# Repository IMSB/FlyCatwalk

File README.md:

FlyCatwalk
==========
This repository contains basic documentation, drawings and code for the **FlyCatwalk**, which was originally developed as a collaboration between the [Institute of Molecular Systems Biology](http://www.imsb.ethz.ch/) at [ETH Zürich](http://www.ethz.ch) and [Scitracks GmbH](http://www.scitracks.com/) 

### License
The **FlyCatwalk** package is licensed by [ETH Zürich](http://www.ethz.ch) under [GPLv3 license](http://www.gnu.org/copyleft/gpl.html)

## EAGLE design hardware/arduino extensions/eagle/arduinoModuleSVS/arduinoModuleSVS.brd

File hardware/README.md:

Hardware
==========
Contains the cad files and the schematics of the arduino extensions required to build the flycatwalk.
The cutting work was done with a laser cutter.

### License
The **FlyCatwalk** package is licensed by [ETH Zürich](http://www.ethz.ch) under [GPLv3 license](http://www.gnu.org/copyleft/gpl.html)

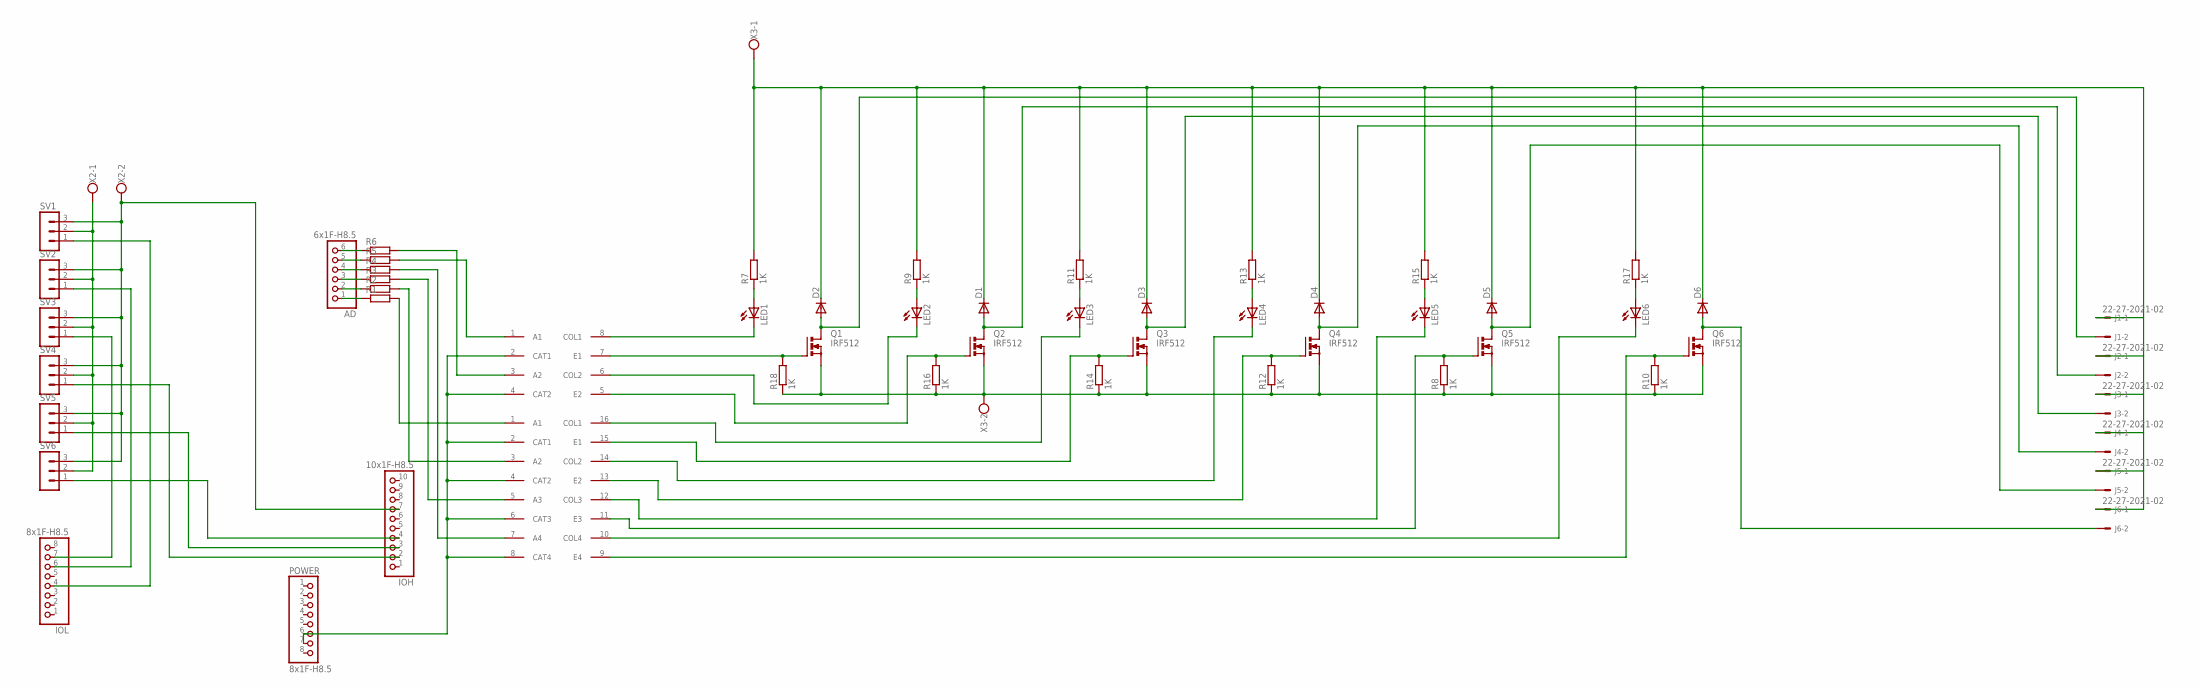
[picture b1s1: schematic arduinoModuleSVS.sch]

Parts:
AD: 6x1F-H8.5; SMARTPRJ_1X06
D1, D2, D3, D4, D5, D6: DIODE-SOD123; SOD123
IOH: 10x1F-H8.5; SMARTPRJ_1X10
IOL: 8x1F-H8.5; SMARTPRJ_1X08
J1, J2, J3, J4, J5, J6: 22-27-2021-02; 6410-02
LED1, LED2, LED3, LED4, LED5, LED6: LED3MM
POWER: 8x1F-H8.5; SMARTPRJ_1X08
Q1, Q2, Q3, Q4, Q5, Q6: IRF512; TO220BV
R1, R2, R3, R4, R5, R6: R-EU_R0805; R0805
R7, R8, R9, R10, R11, R12, R13, R14, R15, R16, R17, R18: 1K; R0805
SV1, SV2, SV3, SV4, SV5, SV6: MA03-1
U$1: ACPL-847-W00E; DIL16
U$2: ACPL-827-00CE; DIL08
X2, X3: W237-102

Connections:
GND: POWER.6, POWER.7, U$1.2 (CAT1), U$1.4 (CAT2), U$1.6 (CAT3), U$1.8 (CAT4), U$2.2 (CAT1), U$2.4 (CAT2)
GND24V: Q1.S, Q2.S, Q3.S, Q4.S, Q5.S, Q6.S, R8.1, R10.1, R12.1, R14.1, R16.1, R18.1, X3.2
GNDARDUINO: IOH.7, SV1.3, SV2.3, SV3.3, SV4.3, SV5.3, SV6.3, X2.2
unnamed: IOL.4, SV1.1
unnamed: IOL.6, SV2.1
unnamed: IOL.7, SV3.1
unnamed: IOH.2, SV4.1
unnamed: IOH.3, SV5.1
unnamed: IOH.4, SV6.1
unnamed: R1.2, U$1.1 (A1)
unnamed: R2.2, U$1.3 (A2)
unnamed: R3.2, U$1.5 (A3)
unnamed: AD.1, R1.1
unnamed: R4.2, U$1.7 (A4)
unnamed: AD.2, R2.1
unnamed: AD.3, R3.1
unnamed: AD.4, R4.1
unnamed: R6.2, U$2.3 (A2)
unnamed: R5.2, U$2.1 (A1)
unnamed: AD.6, R6.1
unnamed: AD.5, R5.1
unnamed: Q1.G, R18.2, U$2.7 (E1)
unnamed: D2.A, J1.2, Q1.D
unnamed: LED2.K (C), U$2.6 (COL2)
unnamed: LED2.A, R9.1
unnamed: Q2.G, R16.2, U$2.5 (E2)
unnamed: LED1.K (C), U$2.8 (COL1)
unnamed: D1.A, J2.2, Q2.D
unnamed: LED1.A, R7.1
unnamed: LED3.K (C), U$1.16 (COL1)
unnamed: LED3.A, R11.1
unnamed: Q3.G, R14.2, U$1.15 (E1)
unnamed: D3.A, J3.2, Q3.D
unnamed: LED4.K (C), U$1.14 (COL2)
unnamed: LED4.A, R13.1
unnamed: Q4.G, R12.2, U$1.13 (E2)
unnamed: D4.A, J4.2, Q4.D
unnamed: LED5.K (C), U$1.12 (COL3)
unnamed: LED5.A, R15.1
unnamed: Q5.G, R8.2, U$1.11 (E3)
unnamed: D5.A, J5.2, Q5.D
unnamed: LED6.K (C), U$1.10 (COL4)
unnamed: LED6.A, R17.1
unnamed: Q6.G, R10.2, U$1.9 (E4)
unnamed: D6.A, J6.2, Q6.D
VCC6V: SV1.2, SV2.2, SV3.2, SV4.2, SV5.2, SV6.2, X2.1
VCC24: D1.C, D2.C, D3.C, D4.C, D5.C, D6.C, J1.1, J2.1, J3.1, J4.1, J5.1, J6.1, R7.2, R9.2, R11.2, R13.2, R15.2, R17.2, X3.1

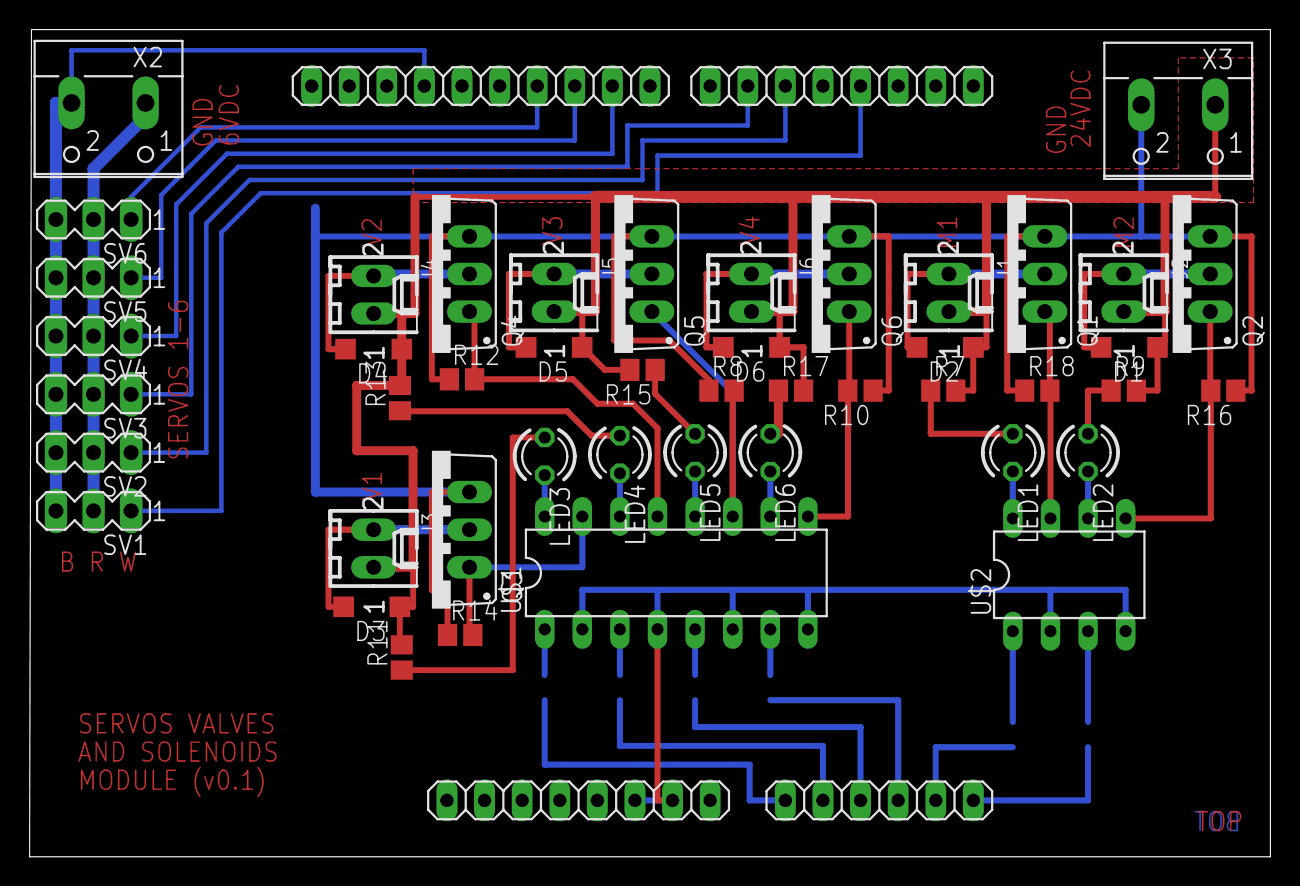
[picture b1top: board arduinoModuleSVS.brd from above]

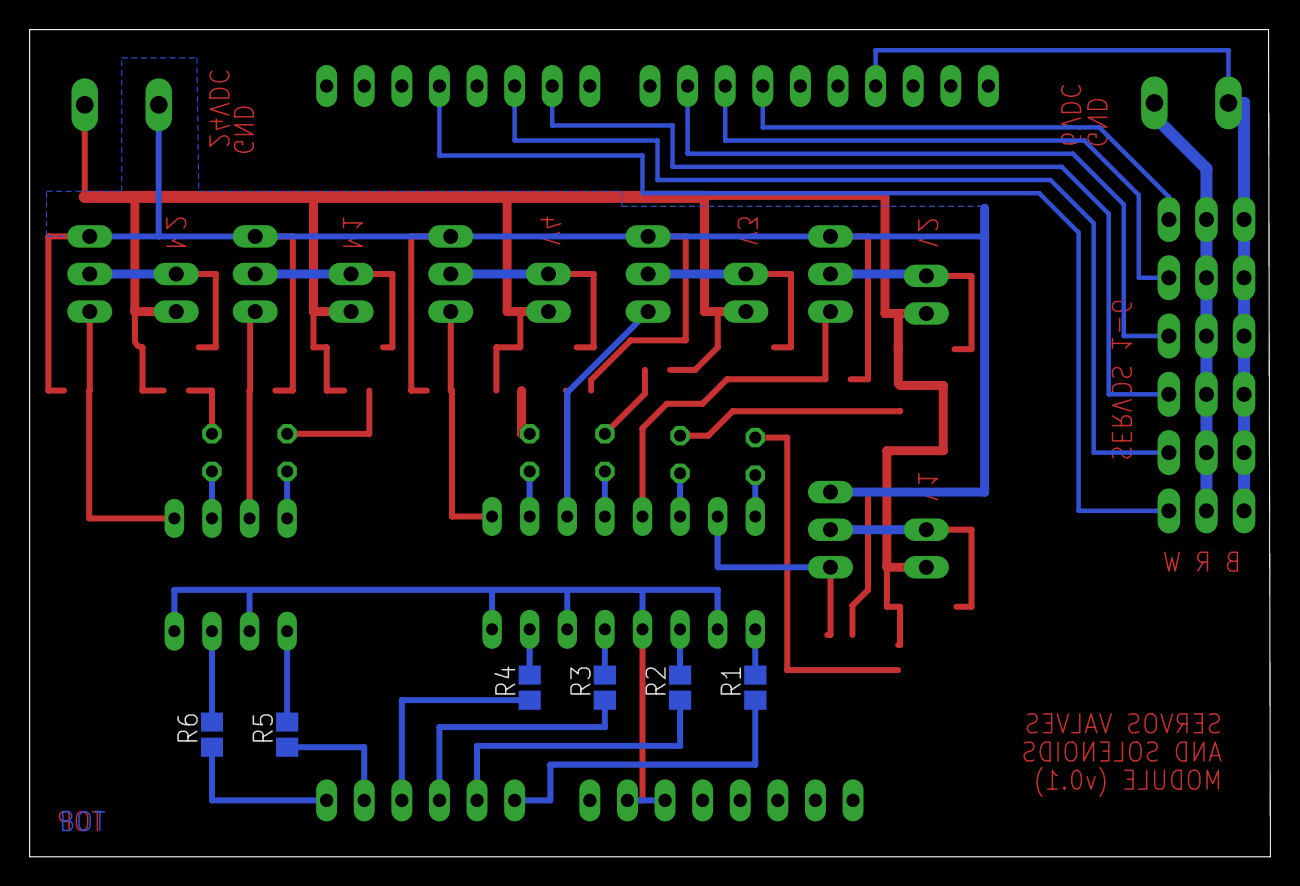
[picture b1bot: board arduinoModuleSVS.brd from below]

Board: 2 copper layers, 83.8 x 55.9 mm, 56 parts (6 on the bottom side), 47 nets.

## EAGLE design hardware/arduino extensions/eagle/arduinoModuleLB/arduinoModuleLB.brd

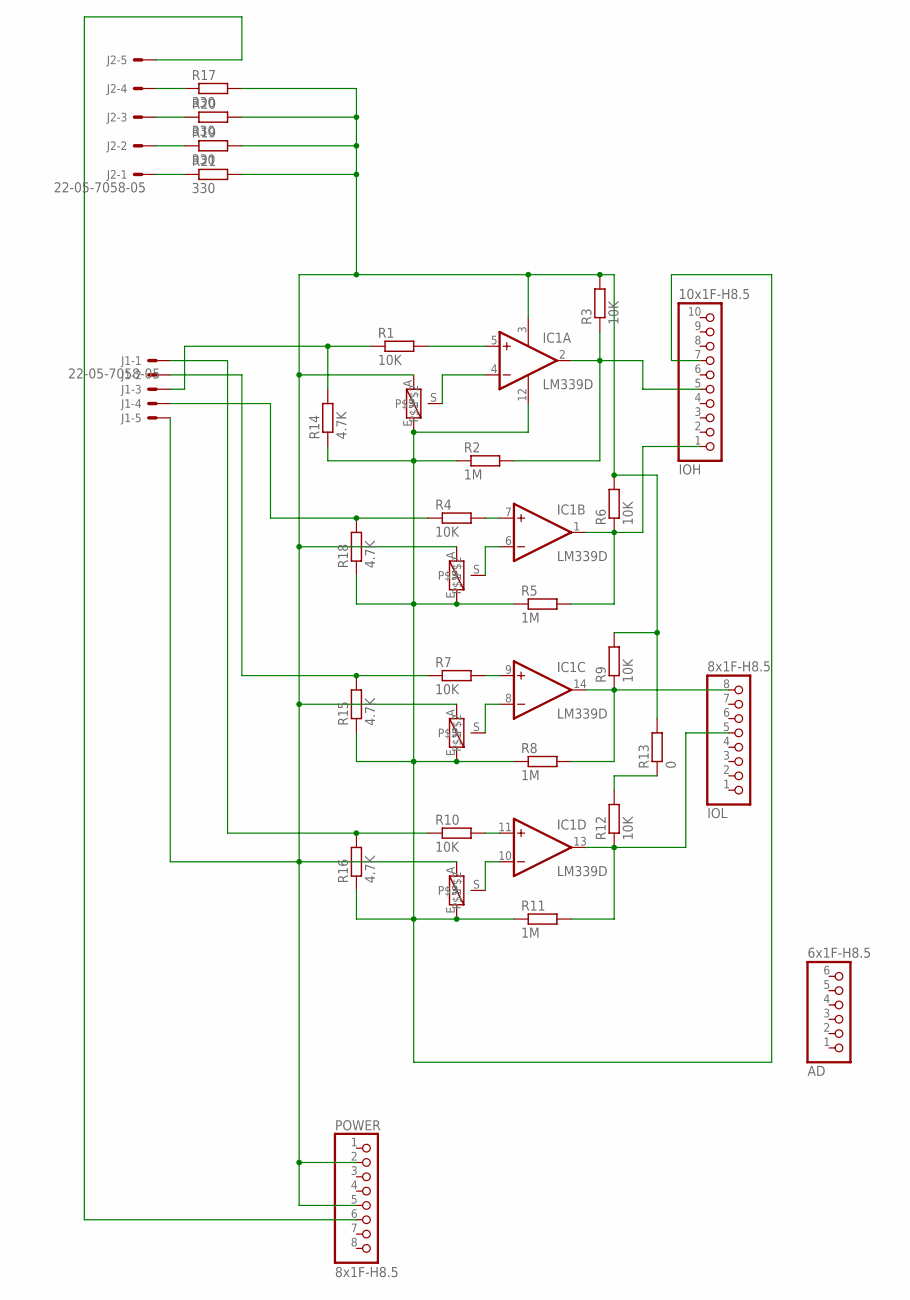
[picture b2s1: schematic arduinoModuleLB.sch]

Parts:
AD: 6x1F-H8.5; SMARTPRJ_1X06
IC1: LM339D; SO14
IOH: 10x1F-H8.5; SMARTPRJ_1X10
IOL: 8x1F-H8.5; SMARTPRJ_1X08
J1, J2: 22-05-7058-05; 7395-05
POWER: 8x1F-H8.5; SMARTPRJ_1X08
R1, R3, R4, R6, R7, R9, R10, R12: 10K; R0603
R2, R5, R8, R11: 1M; R0603
R13: 0; 0207/10
R14, R15, R16, R18: 4.7K; 0207/10
R17, R19, R20, R21: 330; R0603
U$3, U$4, U$5, U$6: M64P103KB40; M64P

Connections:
5V: IC1.3 (V+), J1.5, POWER.2, POWER.5, R3.2, R6.2, R9.2, R13.2, R17.2, R19.2, R20.2, R21.2, U$3.A, U$4.A, U$5.A, U$6.A
GND: IC1.12 (GND), IOH.7, R2.1, R5.1, R8.1, R11.1, R14.1, R15.1, R16.1, R18.1, U$3.E, U$4.E, U$5.E, U$6.E
unnamed: IC1.4 (-IN), U$4.S
unnamed: IC1.5 (+IN), R1.2
unnamed: IC1.2 (OUT), IOH.5, R2.2, R3.1
unnamed: J1.3, R1.1, R14.2
unnamed: IC1.7 (+IN), R4.2
unnamed: IC1.6 (-IN), U$3.S
unnamed: IC1.1 (OUT), IOH.1, R5.2, R6.1
unnamed: J1.4, R4.1, R18.2
unnamed: IC1.8 (-IN), U$5.S
unnamed: IC1.14 (OUT), IOL.8, R8.2, R9.1
unnamed: IC1.10 (-IN), U$6.S
unnamed: J1.2, R7.1, R15.2
unnamed: IC1.9 (+IN), R7.2
unnamed: IC1.13 (OUT), IOL.5, R11.2, R12.1
unnamed: J1.1, R10.1, R16.2
unnamed: R12.2, R13.1
unnamed: IC1.11 (+IN), R10.2
unnamed: J2.4, R17.1
unnamed: J2.3, R20.1
unnamed: J2.2, R19.1
unnamed: J2.1, R21.1
unnamed: J2.5, POWER.6

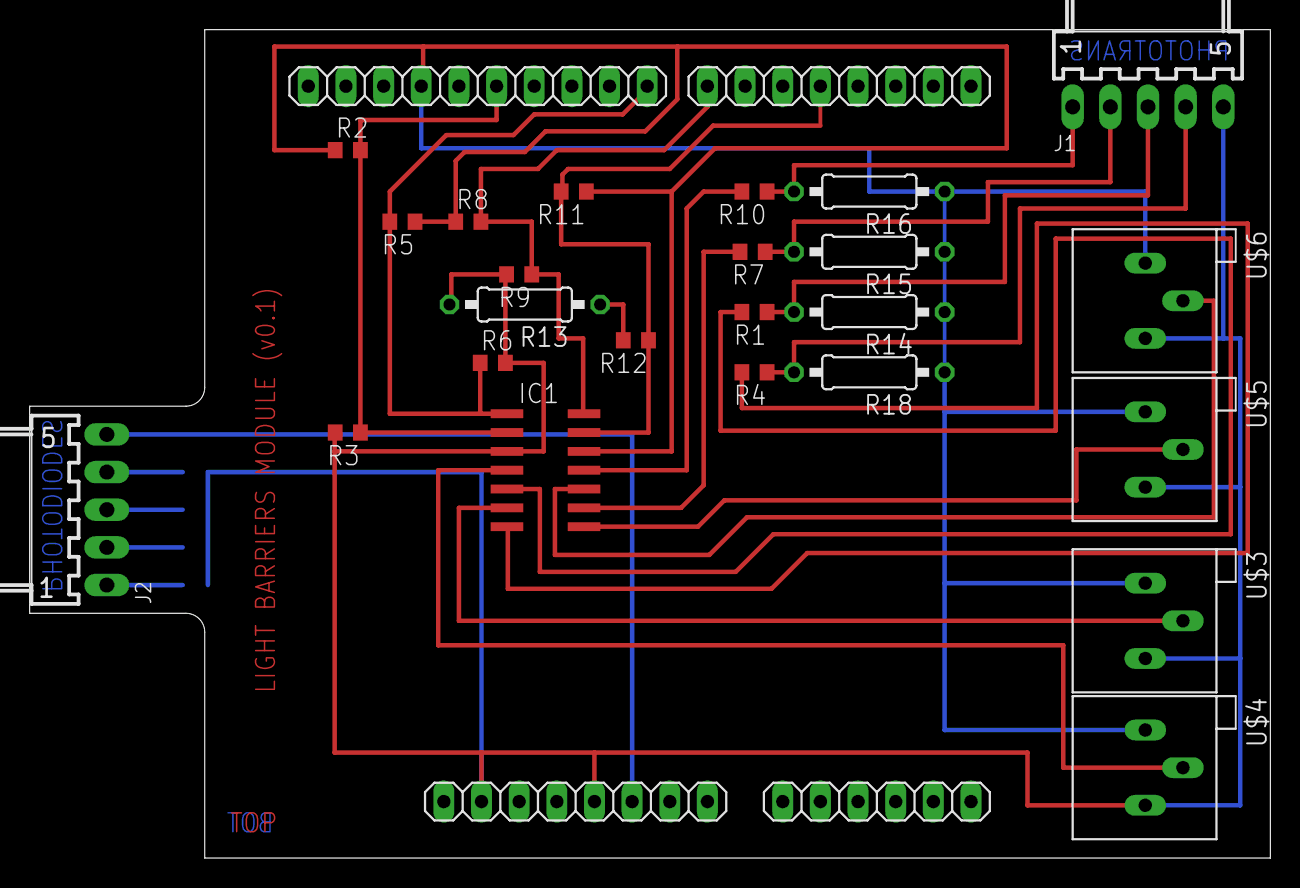
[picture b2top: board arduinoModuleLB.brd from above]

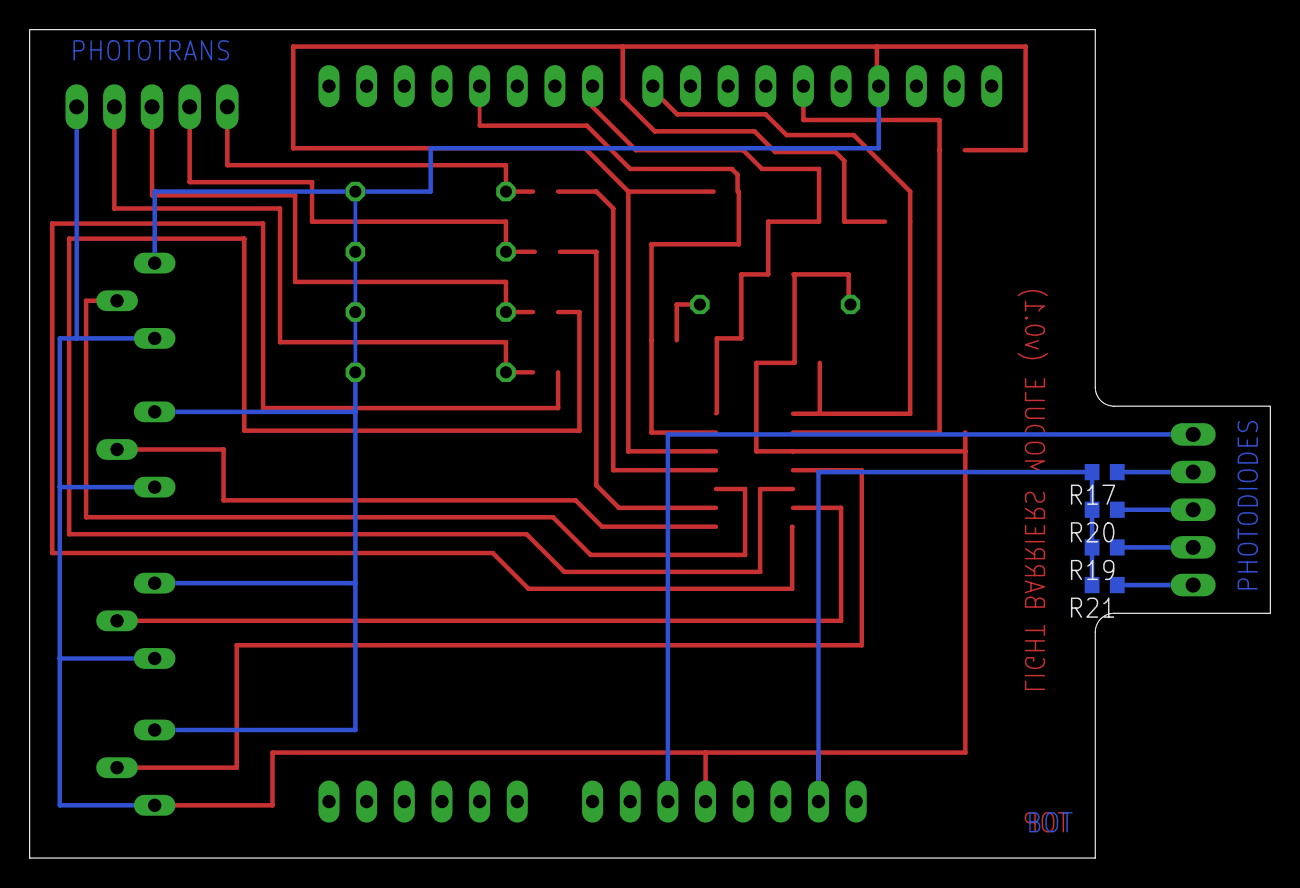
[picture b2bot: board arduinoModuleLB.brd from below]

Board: 2 copper layers, 83.7 x 55.9 mm, 32 parts (4 on the bottom side), 24 nets.

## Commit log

2014-11-16 README
    added Readme file
2014-11-16 hardware
    CAD files and Arduino extension boards
2014-11-16 image processing lib for labview
    Image processing C++ dll for labview for real-time operation
2014-11-16 labview code
    Main project: catWalkArduino.lvproj
2014-11-16 main labview files
    main labview files
2014-11-16 readme
    readme
2014-11-23 matlab
    Code needed to analyze the flycatwalk data.
